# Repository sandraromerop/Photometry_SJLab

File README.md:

# Bpod

Code for Fiber Photometry and Behavioral measurements.

Modified  Bpod code from Kepecs Lab for use in Stephenson-Jones Lab.

( Bpod: from Kepecs Lab workspace, forked from Sanworks)

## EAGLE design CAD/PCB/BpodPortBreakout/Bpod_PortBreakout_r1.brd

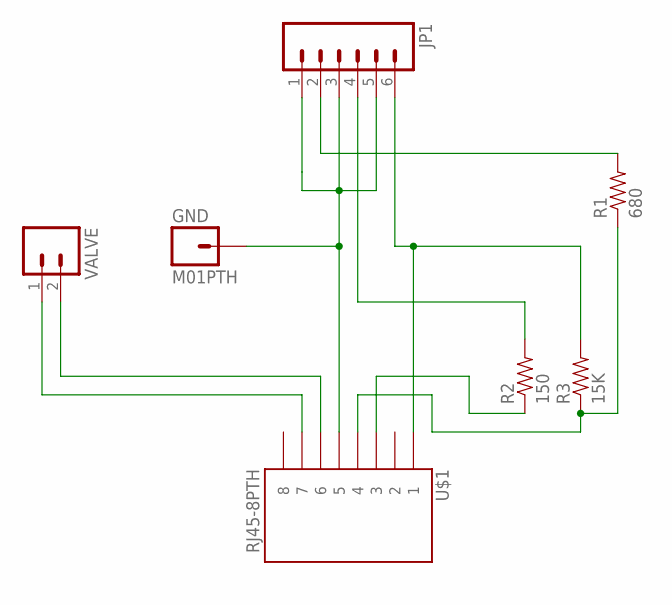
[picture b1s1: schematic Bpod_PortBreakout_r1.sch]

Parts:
GND: M01PTH; 1X01
JP1: M063.5MM-6; SCREWTERMINAL-3.5MM-6
R1: 680; AXIAL-0.4
R2: 150; AXIAL-0.4
R3: 15K; AXIAL-0.4
U$1: RJ45-8PTH; RJ45-8
VALVE: M023.5MM_LOCK; SCREWTERMINAL-3.5MM-2_LOCK

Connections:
unnamed: JP1.6, R3.P$2 (2), U$1.1
unnamed: R1.P$1 (1), R3.P$1 (1), U$1.4
unnamed: JP1.2, R1.P$2 (2)
unnamed: GND.1, JP1.1, JP1.3, JP1.5, U$1.5
unnamed: U$1.6, VALVE.2
unnamed: U$1.7, VALVE.1
unnamed: JP1.4, R2.P$2 (2)
unnamed: R2.P$1 (1), U$1.3

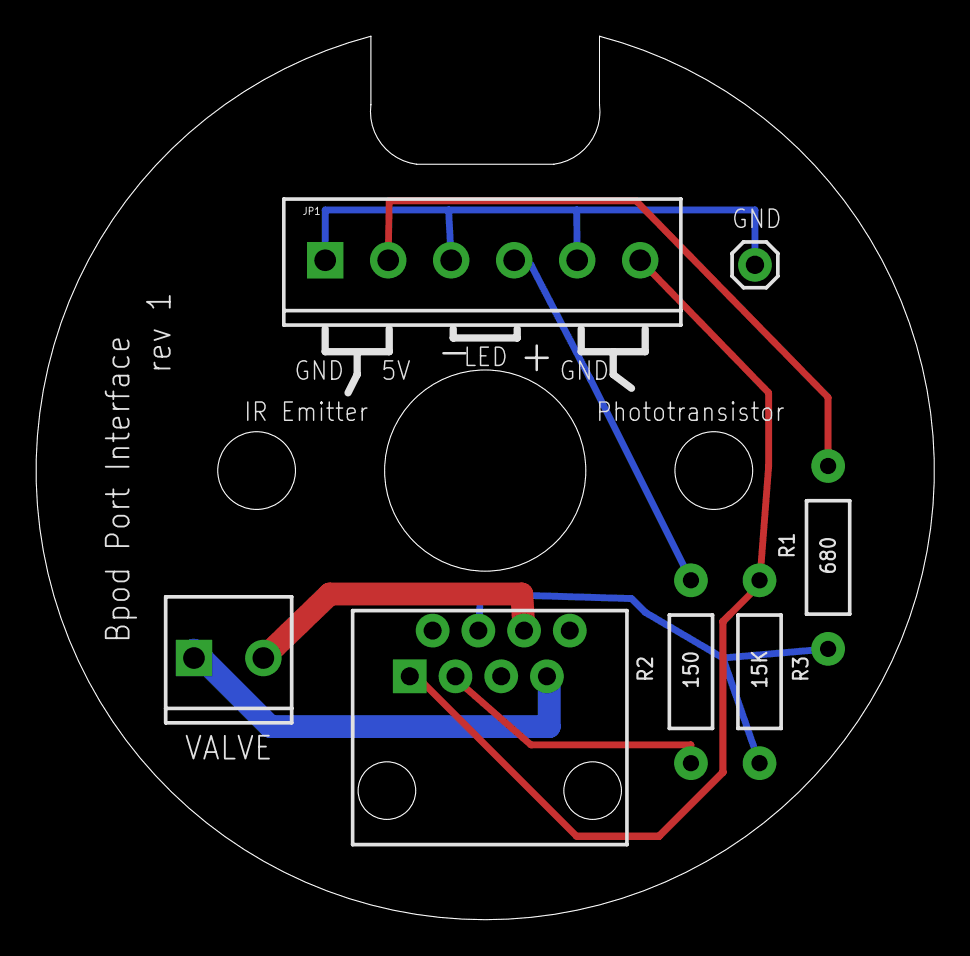
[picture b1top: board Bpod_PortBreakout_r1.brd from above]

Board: 2 copper layers, 49.9 x 49.1 mm, 7 parts (0 on the bottom side), 8 nets.

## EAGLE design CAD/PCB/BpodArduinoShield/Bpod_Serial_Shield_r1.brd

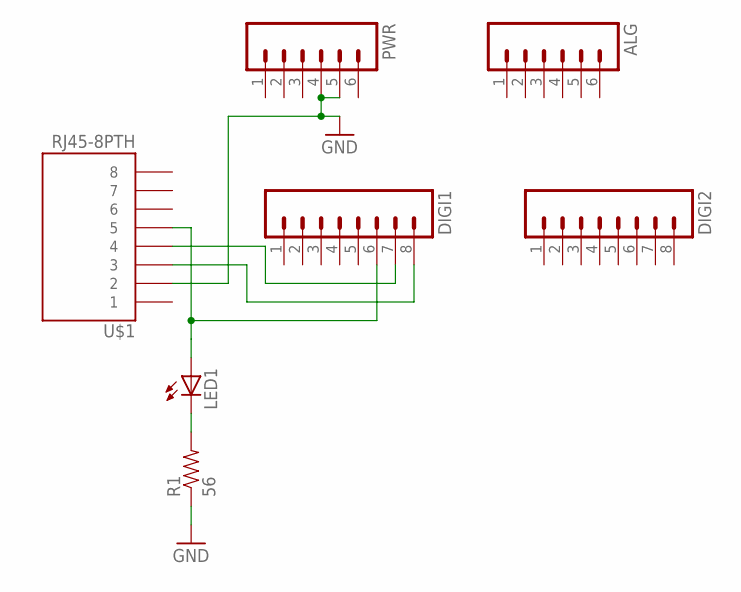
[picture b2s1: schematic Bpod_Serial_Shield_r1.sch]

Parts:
ALG: M06LONGPADS; 1X06_LONGPADS
DIGI1, DIGI2: M08LONGPADS; 1X08_LONGPADS
LED1: LED3MM
PWR: M06LONGPADS; 1X06_LONGPADS
R1: 56; AXIAL-0.3
U$1: RJ45-8PTH; RJ45-8

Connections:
GND: PWR.4, PWR.5, R1.P$1 (1), U$1.2
unnamed: DIGI1.8, U$1.3
unnamed: DIGI1.7, U$1.4
unnamed: DIGI1.6, LED1.A, U$1.5
unnamed: LED1.K (C), R1.P$2 (2)

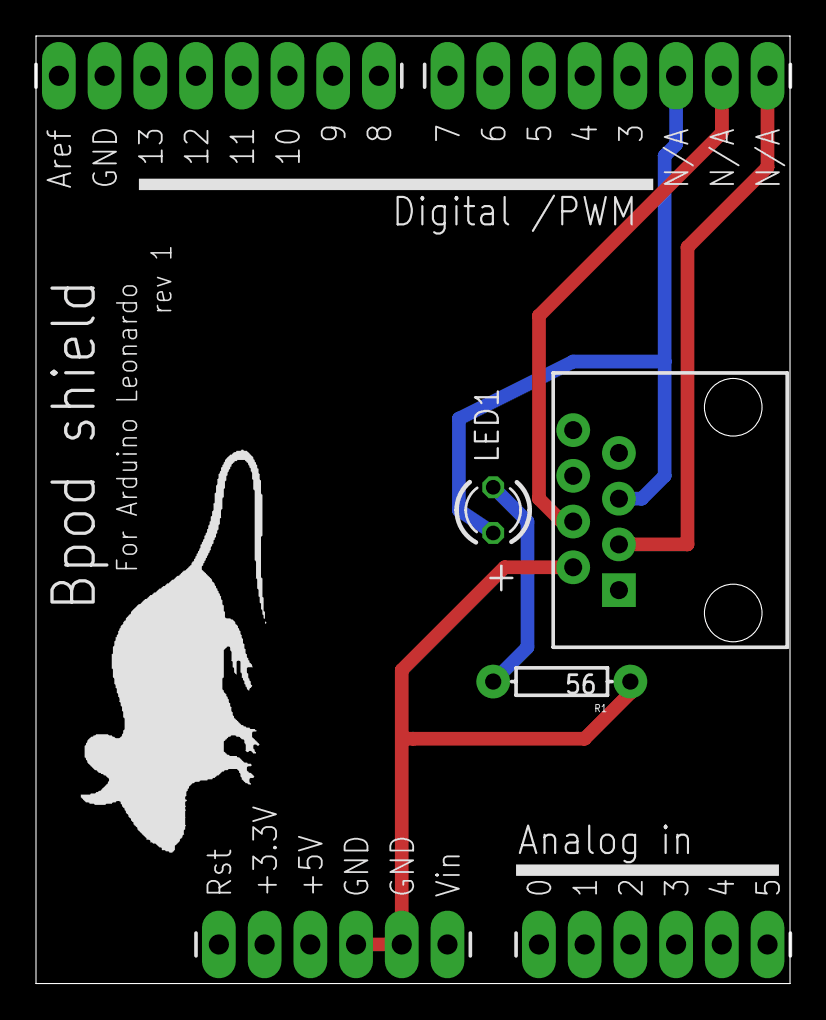
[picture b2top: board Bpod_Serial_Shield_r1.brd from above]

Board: 4 copper layers, 41.9 x 52.6 mm, 8 parts (0 on the bottom side), 5 nets.

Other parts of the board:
U$2: MOUSELOGO

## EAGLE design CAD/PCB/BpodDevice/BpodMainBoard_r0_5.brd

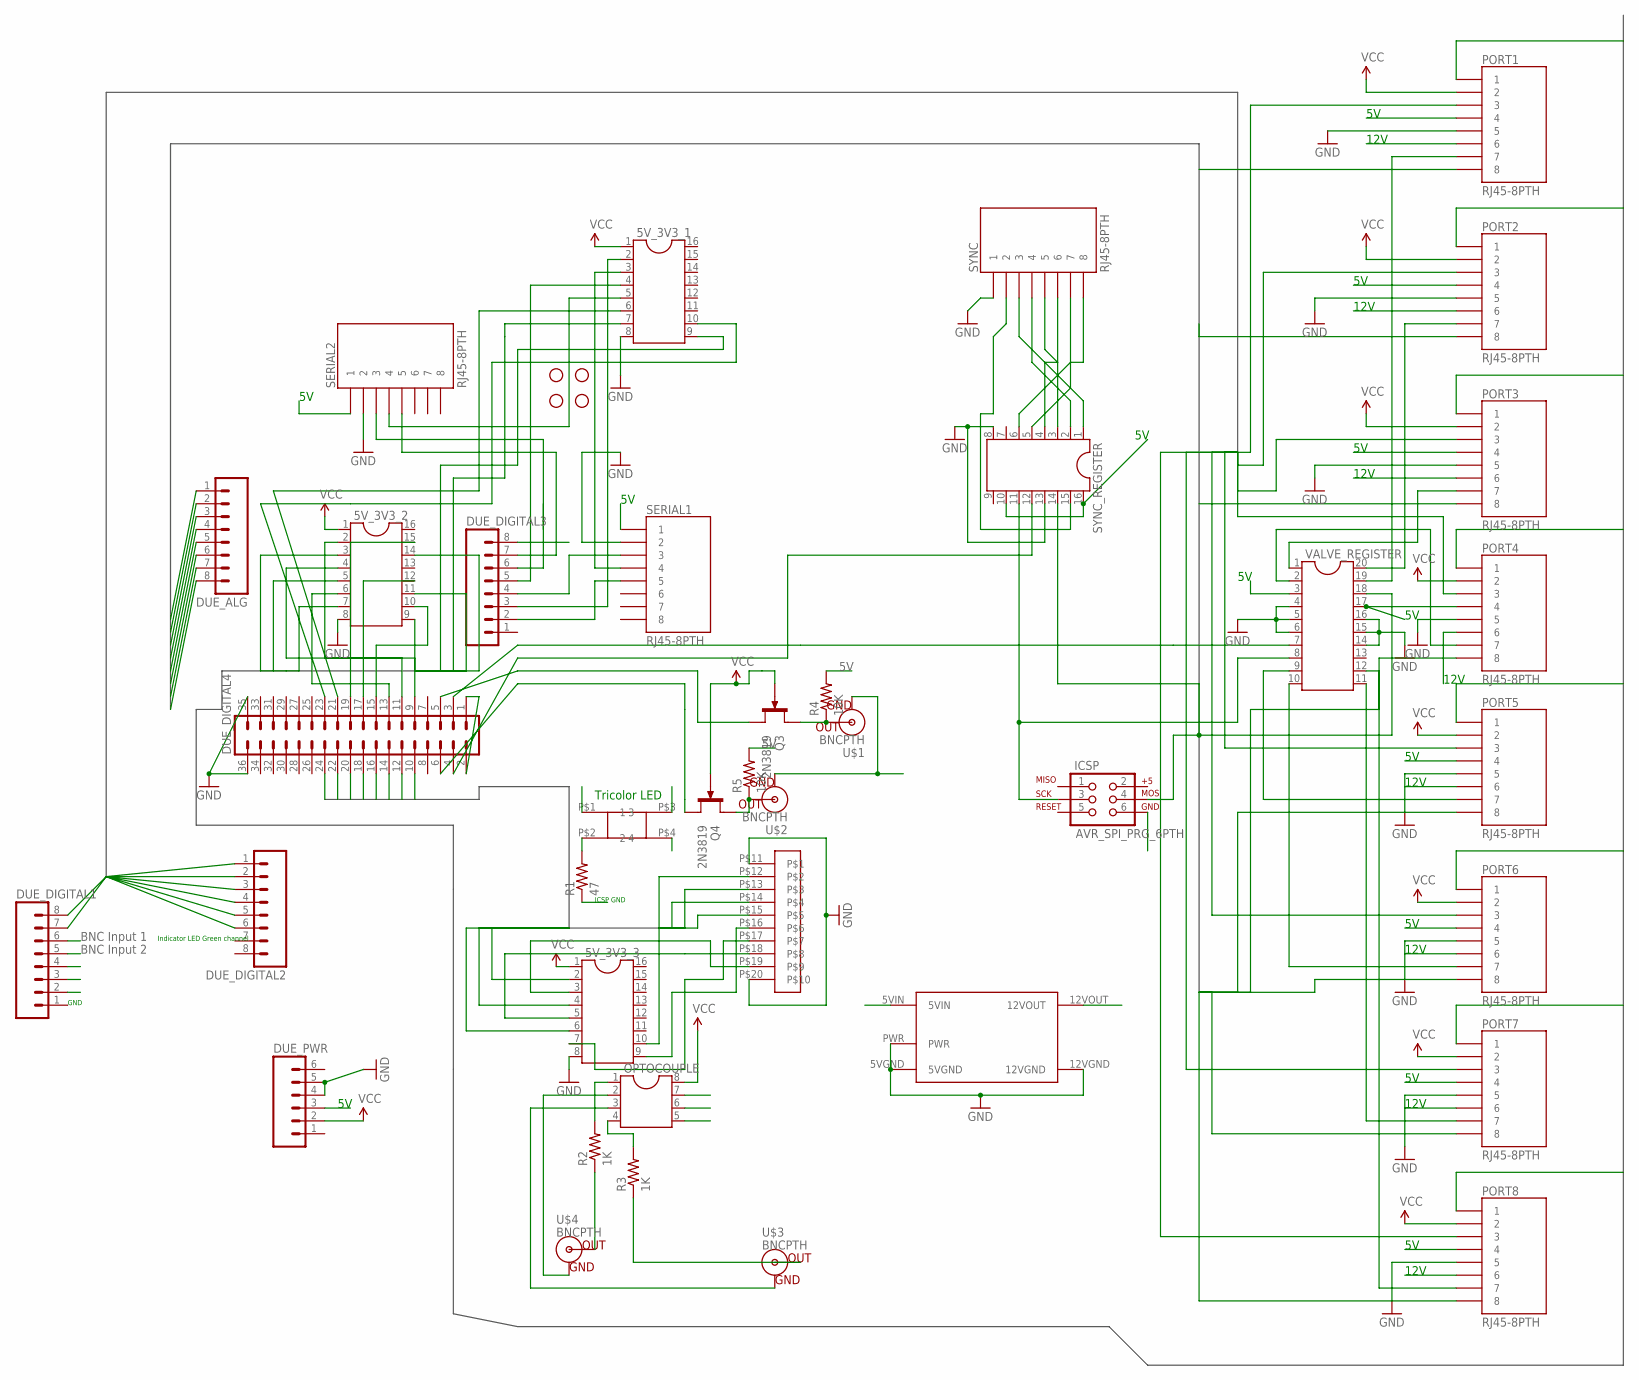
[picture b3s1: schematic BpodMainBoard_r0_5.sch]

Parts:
5V_3V3_1, 5V_3V3_2, 5V_3V3_3: DIL16
DUE_ALG: M081X08; 1X08
DUE_DIGITAL1, DUE_DIGITAL2, DUE_DIGITAL3: M081X08; 1X08
DUE_DIGITAL4: MA18-2
DUE_PWR: M06SIP; 1X06
ICSP: AVR_SPI_PRG_6PTH; 2X3
JP1, JP2, JP3, JP4: STAND-OFF
OPTOCOUPLE: DIL8; DIL08
PORT1, PORT2, PORT3, PORT4, PORT5, PORT6, PORT7, PORT8: RJ45-8PTH; RJ45-8
Q3, Q4: 2N3819; TO92F
R1: 47; AXIAL-0.3
R2, R3: 1K; AXIAL-0.3
R4, R5: 10K; AXIAL-0.3
SERIAL1, SERIAL2: RJ45-8PTH; RJ45-8
SYNC: RJ45-8PTH; RJ45-8
SYNC_REGISTER: DIL16
U$1, U$2, U$3, U$4: BNCPTH; BNC
U$5: TDK_LAMBDA_5V_TO_12V; TDK_LAMBDA_5V_12V
U$6: 10POS_SPRING_TERMINAL; 10POS_SCREW_TERMINAL
U$8: SQUARE_TRICOLOR_LED
VALVE_REGISTER: DIL20

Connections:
5V: DUE_DIGITAL4.1, DUE_DIGITAL4.2, DUE_PWR.3, PORT1.4, PORT2.4, PORT3.4, PORT4.4, PORT5.4, PORT6.4, PORT7.4, PORT8.4, R4.P$2 (2), R5.P$2 (2), SERIAL1.1, SERIAL2.1, SYNC_REGISTER.10, SYNC_REGISTER.16, U$5.5VIN, VALVE_REGISTER.3, VALVE_REGISTER.17
12V: PORT1.6, PORT2.6, PORT3.6, PORT4.6, PORT5.6, PORT6.6, PORT7.6, PORT8.6, U$5.12VOUT
ANALOG_BUS1: DUE_ALG.1, PORT1.8
ANALOG_BUS2: DUE_ALG.2, PORT2.8
ANALOG_BUS3: DUE_ALG.3, PORT3.8
ANALOG_BUS4: DUE_ALG.4, PORT4.8
ANALOG_BUS5: DUE_ALG.5, PORT5.8
ANALOG_BUS6: DUE_ALG.6, PORT6.8
ANALOG_BUS7: DUE_ALG.7, PORT7.8
ANALOG_BUS8: DUE_ALG.8, PORT8.8
BNCIN1: DUE_DIGITAL1.6, OPTOCOUPLE.7
BNCIN2: DUE_DIGITAL1.5, OPTOCOUPLE.6
DIGITAL_BUS1: 5V_3V3_2.3, PORT1.1
DIGITAL_BUS2: 5V_3V3_2.5, PORT2.1
DIGITAL_BUS3: 5V_3V3_2.7, PORT3.1
DIGITAL_BUS4: 5V_3V3_2.9, PORT4.1
DIGITAL_BUS5: 5V_3V3_2.11, PORT5.1
DIGITAL_BUS6: 5V_3V3_2.14, PORT6.1
DIGITAL_BUS7: 5V_3V3_1.7, PORT7.1
DIGITAL_BUS8: 5V_3V3_1.9, PORT8.1
DSUB_BUS1: 5V_3V3_3.2, DUE_DIGITAL4.10
DSUB_BUS2: 5V_3V3_3.4, DUE_DIGITAL4.12
DSUB_BUS3: 5V_3V3_3.6, DUE_DIGITAL4.14
DSUB_BUS4: 5V_3V3_3.10, DUE_DIGITAL4.16
DSUB_BUS5: DUE_DIGITAL4.18, U$6.P$15
DSUB_BUS6: DUE_DIGITAL4.20, U$6.P$14
DSUB_BUS7: DUE_DIGITAL4.22, U$6.P$13
DSUB_BUS8: DUE_DIGITAL4.24, U$6.P$12
GND: 5V_3V3_1.8, 5V_3V3_2.8, 5V_3V3_3.8, DUE_DIGITAL4.35, DUE_DIGITAL4.36, DUE_PWR.4, DUE_PWR.5, PORT1.5, PORT2.5, PORT3.5, PORT4.5, PORT5.5, PORT6.5, PORT7.5, PORT8.5, SERIAL1.2, SERIAL2.2, SYNC.1, SYNC_REGISTER.8, SYNC_REGISTER.13, U$5.5VGND, U$5.12VGND, U$5.PWR, U$6.P$11, U$6.P$20, VALVE_REGISTER.4, VALVE_REGISTER.5, VALVE_REGISTER.6, VALVE_REGISTER.14, VALVE_REGISTER.15, VALVE_REGISTER.16
ICSP_GND: ICSP.6, R1.P$1 (1)
LED1: DUE_DIGITAL1.4, U$8.P$3 (3)
LED2: DUE_DIGITAL1.3, U$8.P$4 (4)
LED3: DUE_DIGITAL3.8, U$8.P$1 (1)
LED_BUS1: DUE_DIGITAL1.7, PORT1.3
LED_BUS2: DUE_DIGITAL1.8, PORT2.3
LED_BUS3: DUE_DIGITAL2.1, PORT3.3
LED_BUS4: DUE_DIGITAL2.2, PORT4.3
LED_BUS5: DUE_DIGITAL2.3, PORT5.3
LED_BUS6: DUE_DIGITAL2.4, PORT6.3
LED_BUS7: DUE_DIGITAL2.5, PORT7.3
LED_BUS8: DUE_DIGITAL2.6, PORT8.3
unnamed: R2.P$1 (1), U$4.S (OUT)
unnamed: R3.P$1 (1), U$3.S (OUT)
unnamed: OPTOCOUPLE.1, R2.P$2 (2)
unnamed: OPTOCOUPLE.4, R3.P$2 (2)
unnamed: OPTOCOUPLE.2, U$4.GND
unnamed: OPTOCOUPLE.3, U$3.GND
unnamed: Q3.D, R4.P$1 (1), U$1.S (OUT)
unnamed: Q4.D, R5.P$1 (1), U$2.S (OUT)
unnamed: PORT1.7, VALVE_REGISTER.19
unnamed: PORT2.7, VALVE_REGISTER.20
unnamed: PORT3.7, VALVE_REGISTER.1
unnamed: PORT4.7, VALVE_REGISTER.2
unnamed: PORT5.7, VALVE_REGISTER.9
unnamed: PORT6.7, VALVE_REGISTER.10
unnamed: PORT7.7, VALVE_REGISTER.11
unnamed: PORT8.7, VALVE_REGISTER.12
unnamed: SYNC.2, SYNC_REGISTER.15
unnamed: SYNC.3, SYNC_REGISTER.1
unnamed: SYNC.4, SYNC_REGISTER.2
unnamed: DUE_DIGITAL4.3, VALVE_REGISTER.7
unnamed: SYNC.5, SYNC_REGISTER.3
unnamed: SYNC.6, SYNC_REGISTER.4
unnamed: SYNC.7, SYNC_REGISTER.5
unnamed: SYNC.8, SYNC_REGISTER.6
unnamed: R1.P$2 (2), U$8.P$2 (2)
unnamed: DUE_DIGITAL4.5, Q3.S
unnamed: DUE_DIGITAL4.4, SYNC_REGISTER.12
unnamed: DUE_DIGITAL4.6, Q4.S
unnamed: 5V_3V3_1.3, SERIAL1.4
unnamed: 5V_3V3_1.2, DUE_DIGITAL3.3
unnamed: DUE_DIGITAL3.4, SERIAL1.3
unnamed: 5V_3V3_1.5, SERIAL2.4
unnamed: 5V_3V3_1.4, DUE_DIGITAL3.5
unnamed: DUE_DIGITAL3.2, SERIAL1.5
unnamed: 5V_3V3_1.6, DUE_DIGITAL4.21
unnamed: DUE_DIGITAL3.6, SERIAL2.3
unnamed: 5V_3V3_1.10, DUE_DIGITAL4.23
unnamed: DUE_DIGITAL3.7, SERIAL2.5
unnamed: 5V_3V3_2.2, DUE_DIGITAL4.9
unnamed: 5V_3V3_2.4, DUE_DIGITAL4.11
unnamed: 5V_3V3_2.6, DUE_DIGITAL4.13
unnamed: 5V_3V3_2.10, DUE_DIGITAL4.15
unnamed: 5V_3V3_2.12, DUE_DIGITAL4.17
unnamed: 5V_3V3_2.15, DUE_DIGITAL4.19
unnamed: 5V_3V3_3.3, U$6.P$19
unnamed: 5V_3V3_3.5, U$6.P$18
unnamed: 5V_3V3_3.7, U$6.P$17
unnamed: 5V_3V3_3.9, U$6.P$16
SPI_CLK: ICSP.3, SYNC_REGISTER.11, VALVE_REGISTER.8
SPI_DATA: ICSP.4, SYNC_REGISTER.14, VALVE_REGISTER.18
UPPER_GND: DUE_DIGITAL1.2, OPTOCOUPLE.5, U$1.GND, U$2.GND
VCC: 5V_3V3_1.1, 5V_3V3_2.1, 5V_3V3_3.1, DUE_PWR.2, OPTOCOUPLE.8, PORT1.2, PORT2.2, PORT3.2, PORT4.2, PORT5.2, PORT6.2, PORT7.2, PORT8.2, Q3.G, Q4.G

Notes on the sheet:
12V
BNC Input 1
BNC Input 2
Indicator LED Green channel
Tricolor LED
ICSP GND
GND

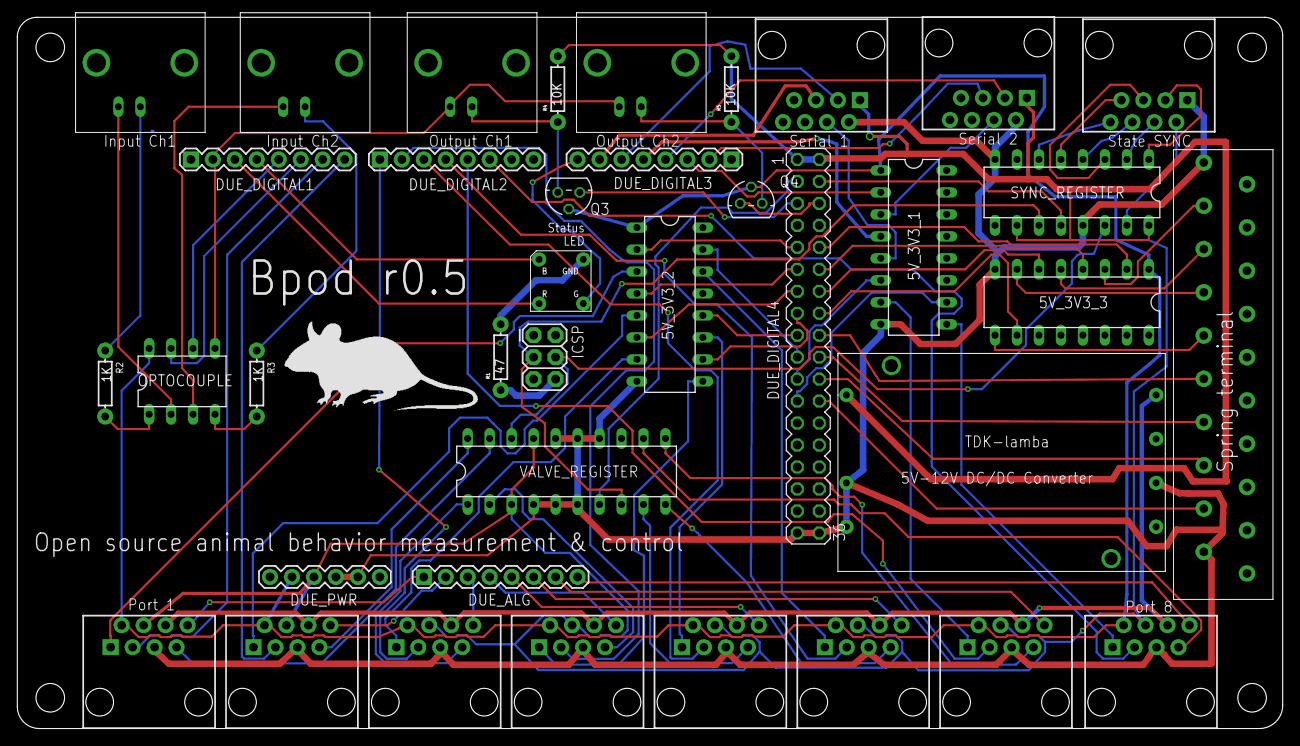
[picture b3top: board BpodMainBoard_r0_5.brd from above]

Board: 2 copper layers, 146.3 x 82.2 mm, 43 parts (0 on the bottom side), 93 nets.

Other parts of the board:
U$7: MOUSELOGO

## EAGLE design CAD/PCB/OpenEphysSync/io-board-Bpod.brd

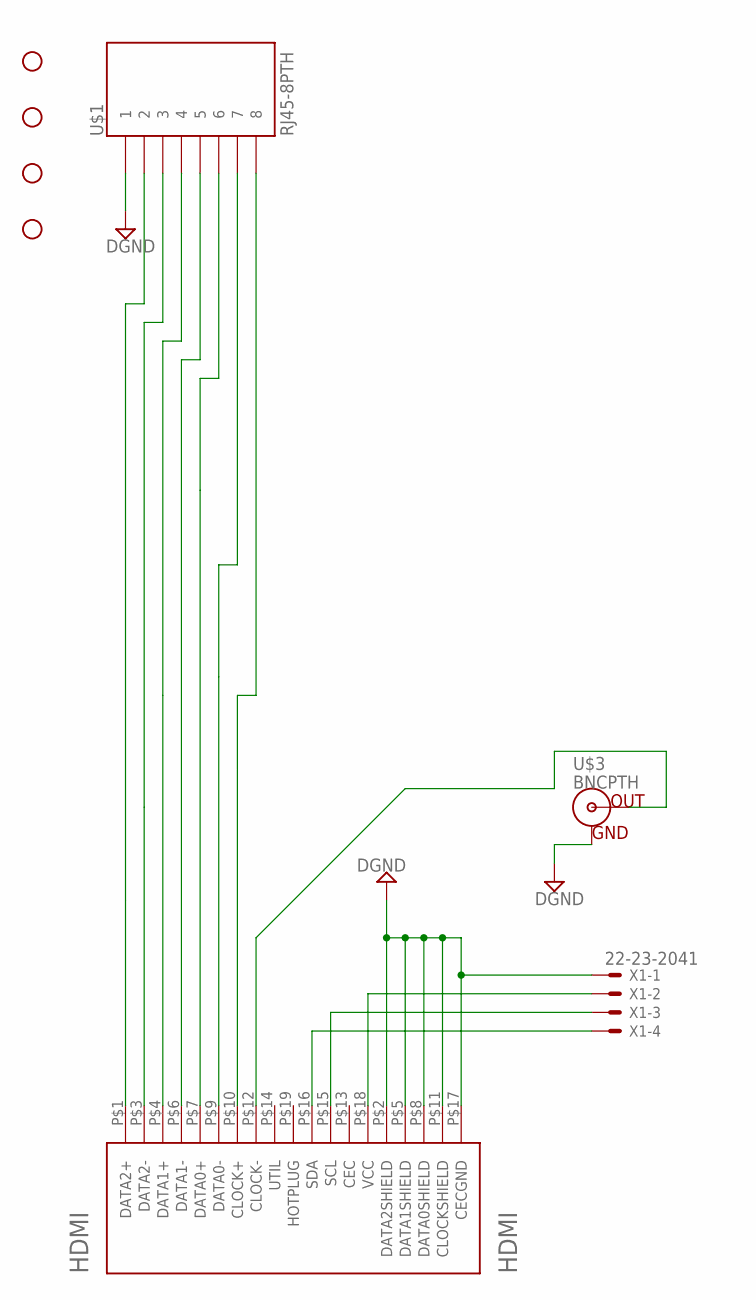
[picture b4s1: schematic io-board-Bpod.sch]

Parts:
HDMI: HDMI; HDMI_A
STANDOFF1, STANDOFF2, STANDOFF3, STANDOFF4: STAND-OFF
U$1: RJ45-8PTH; RJ45-8
U$3: BNCPTH; BNC
X1: 22-23-2041

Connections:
CH6: HDMI.P$9 (DATA0-), U$1.7
DGND: HDMI.P$2 (DATA2SHIELD), HDMI.P$5 (DATA1SHIELD), HDMI.P$8 (DATA0SHIELD), HDMI.P$11 (CLOCKSHIELD), HDMI.P$17 (CECGND), U$1.1, U$3.GND, X1.1
I2C_CLK: HDMI.P$15 (SCL), X1.3
I2C_DAT: HDMI.P$16 (SDA), X1.4
unnamed: HDMI.P$12 (CLOCK-), U$3.S (OUT)
unnamed: HDMI.P$4 (DATA1+), U$1.4
unnamed: HDMI.P$3 (DATA2-), U$1.3
unnamed: HDMI.P$1 (DATA2+), U$1.2
unnamed: HDMI.P$7 (DATA0+), U$1.6
unnamed: HDMI.P$10 (CLOCK+), U$1.8
unnamed: HDMI.P$6 (DATA1-), U$1.5
VCC: HDMI.P$18 (VCC), X1.2

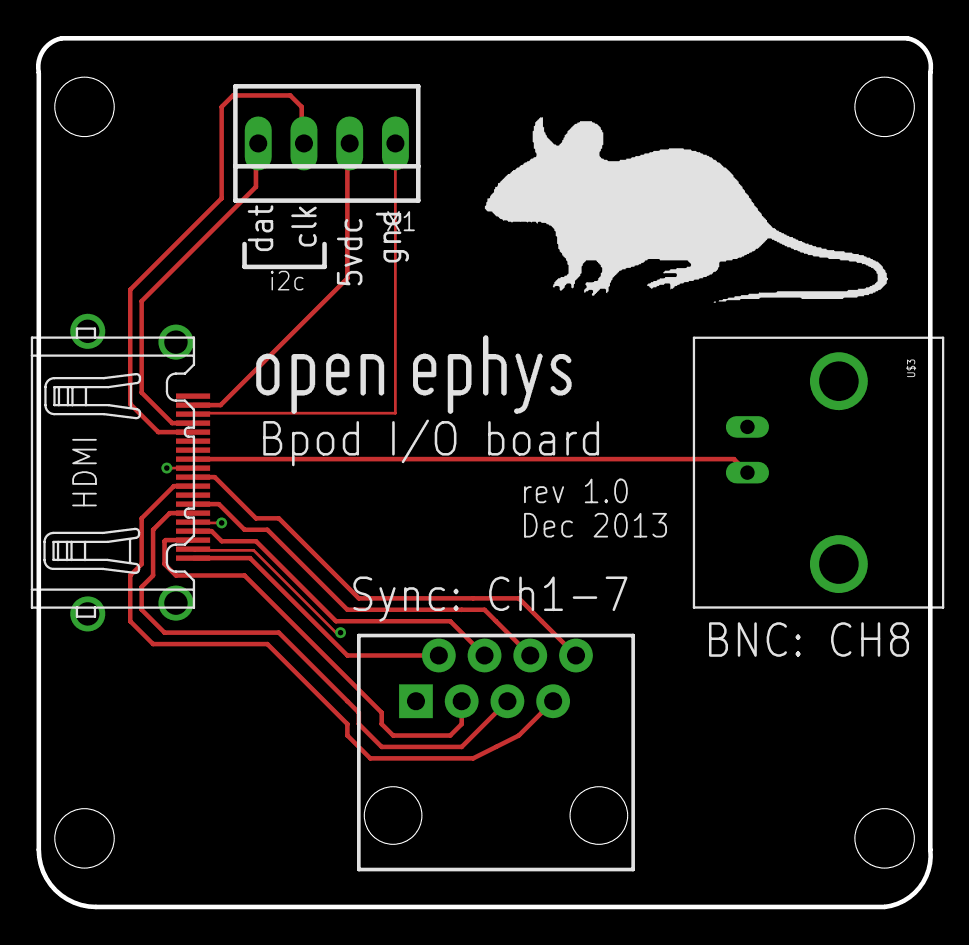
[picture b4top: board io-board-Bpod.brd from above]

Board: 4 copper layers, 49.6 x 48.3 mm, 10 parts (0 on the bottom side), 12 nets.

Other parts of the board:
U$2: OPEN_EPHYS_LOGO
U$4: MOUSELOGO

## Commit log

2018-05-29 Code for photometry customized with Optogenetics
2018-05-30 Add files via upload
    Analysis code for photometry and behavior acquired with bpod
2018-06-03 no message
2018-06-05 Wheel for optogenetics
2018-07-07 Plotting including hit/miss
2018-07-07 to generate block sequence and gaussian distribution of a set of values
2018-07-07 self-stimulation analysis
2018-07-07 Cued_reward script suitable for new plotting
2018-07-07 Trial Settings for new task
2018-07-07 Back propagation task
2018-07-07 Self stimulation task
2018-07-07 BeliefState task
2018-07-07 updated to plots
2018-07-07 modified beleifstate
2018-07-12 test
2018-07-12 Updates on plots
2018-07-12 trial settings savings
2018-07-12 Calibration files
2018-07-12 setting files
2018-07-12 Cued reward protocol - Fred modified
2018-07-12 task parameters
2018-07-12 updated settings belief state
2018-07-12 working copy
2018-07-12 With new trial settings saving
2018-07-12 Add files via upload
    Calibration files
2018-07-31 BeliefState analysis
2018-07-31 allign traces
2018-07-31 helpers
2018-07-31 self stim analysis
2018-07-31 trial settings
2018-07-31 analysis modifications
2018-08-01 Made the code flexible such that it requires the behaviour data path as user input but will then find the mouse ID itself. Should be compatible across platforms
2018-08-01 Fixed indexing bug in pulling out mouse name
2018-08-01 fixed some cross platform issues and tried to document
2018-08-02 Allign traces option for if there is no photometry
2018-08-02 Gave option to run with or without photometry data
2018-08-02 removed line repetition
2018-08-06 Operant task

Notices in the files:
parts and their libraries:
SparkFun: Licensing: CC v3.0 Share-Alike You are welcome to use this library for commercial purposes.
